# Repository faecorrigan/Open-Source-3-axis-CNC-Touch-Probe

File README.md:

# Open-Source-3-axis-CNC-Touch-Probe

This is a 3 axis cnc probe, principle development is done for the Makera Carvera

Features:
wireless communication between the probe and host via raw 802.15.4 packets
OTA firmware configuration and updates
wireless charging of on board lipo battery

The current development prototype in software uses the Arduino IDE with a seedstudio XIAO nrf52840 
Final hardware will be a custom nrf52840 circuit. 

the project currently is using public libraries from:
https://github.com/Tjoms99/xiao_sense_nrf52840_battery_lib

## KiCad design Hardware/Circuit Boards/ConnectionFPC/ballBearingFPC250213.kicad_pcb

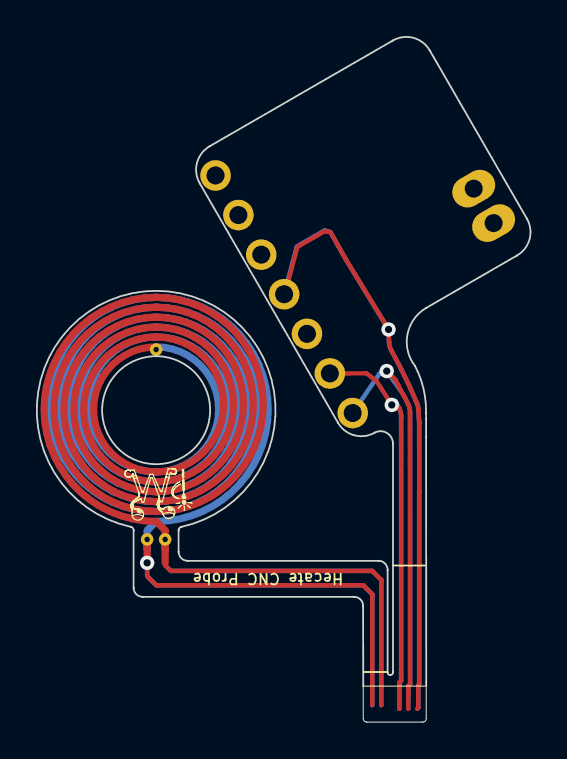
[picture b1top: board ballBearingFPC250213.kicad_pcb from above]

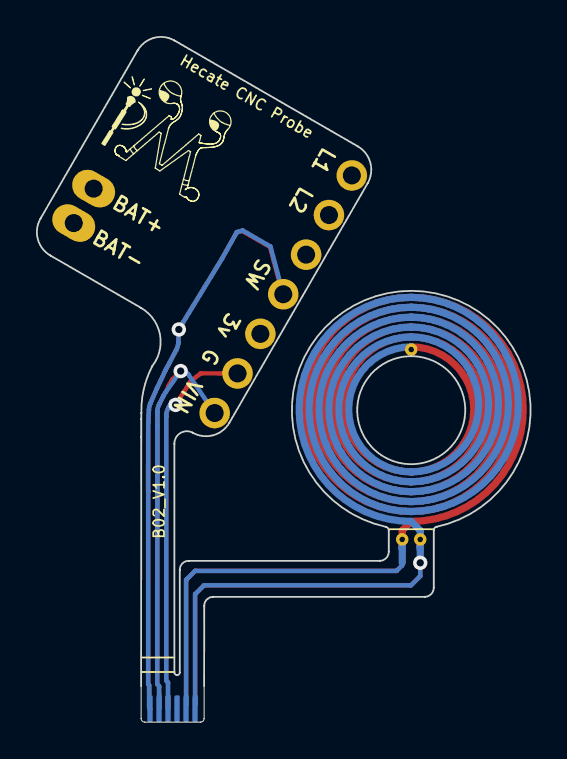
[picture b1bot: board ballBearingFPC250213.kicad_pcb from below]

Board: 2 copper layers, 27.4 x 38.1 mm, 11 parts (11 on the bottom side), 5 nets.

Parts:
J1: BB Board FPC Connection; FPC Cable End For JUSHUO AFH34 JLCPCP C5139821
J1#2: 3v; 2.54mm Flex PCB Solder Hole
J2: Xiao GND; 2.54mm Flex PCB Solder Hole
J3: Xiao VUSB; 2.54mm Flex PCB Solder Hole
J4: Xiao Switch; 2.54mm Flex PCB Solder Hole
J5: Las01; 2.54mm Flex PCB Solder Hole
J6: Las02; 2.54mm Flex PCB Solder Hole
J7: Empty; 2.54mm Flex PCB Solder Hole
J8: Bat+; 2.54mm Flex PCB Solder Hole
J9: Bat-; 2.54mm Flex PCB Solder Hole
L2: Wireless Charging Coil; COIL_GENERATOR_1

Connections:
unnamed: J1.1, J1#2.1, J4.1
unnamed: J1.2, J3.1
unnamed: J1.3, J2.1
unnamed: J1.5, L2.2
unnamed: J1.6, L2.1

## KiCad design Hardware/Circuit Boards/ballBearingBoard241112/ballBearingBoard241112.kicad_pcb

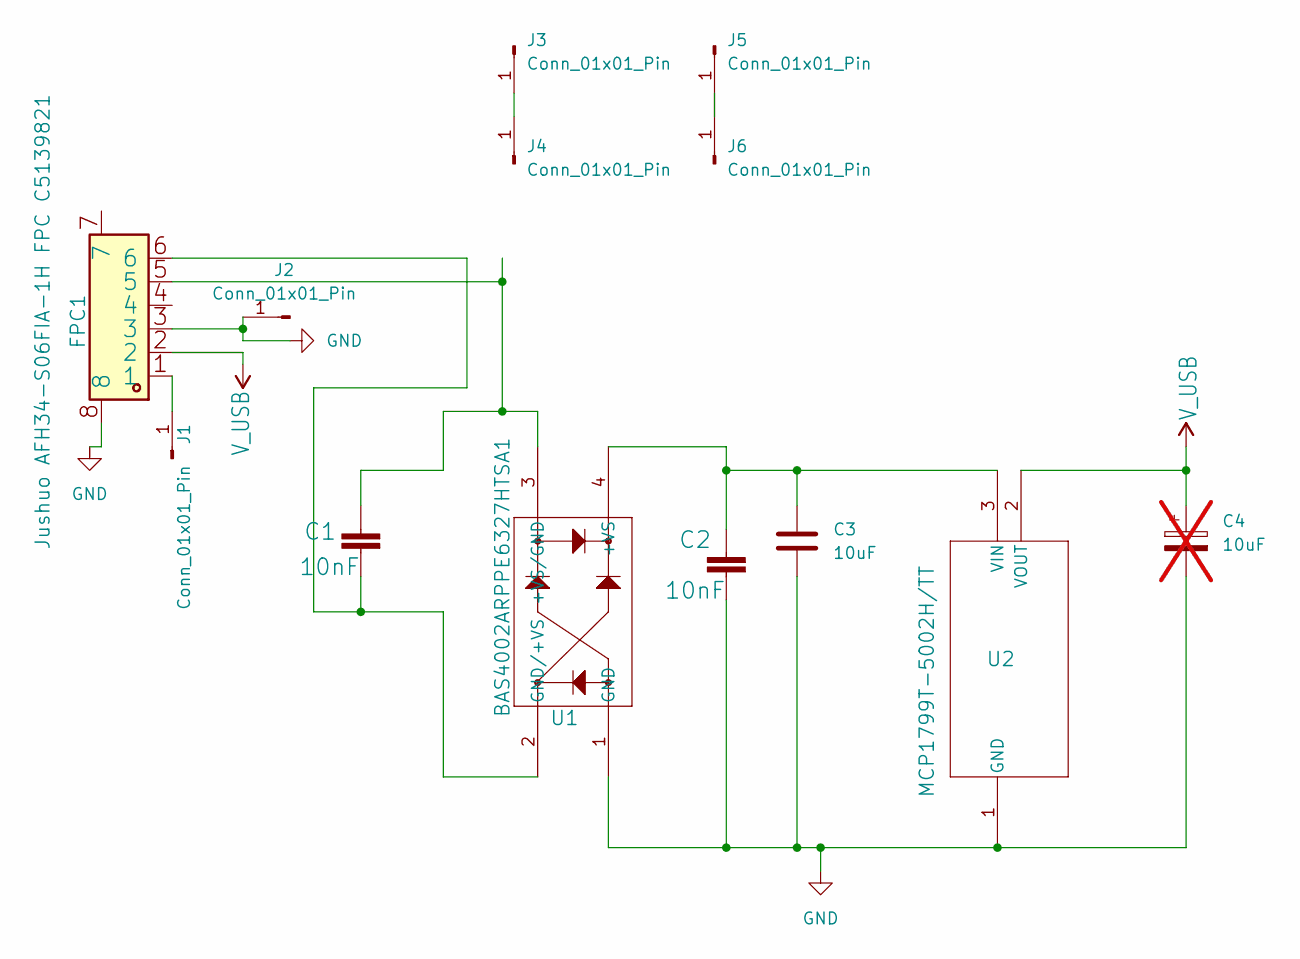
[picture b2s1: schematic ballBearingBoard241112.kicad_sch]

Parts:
C1, C2: 10nF; C_0402_1005Metric; LCSC C15195
C3: 10uF; C_0402_1005Metric; LCSC C15195
C4: 10uF; C_0603_1608Metric; not fitted
FPC1: Jushuo AFH34-S06FIA-1H FPC C5139821; LCSC C5139821
J1, J2, J3, J4, J5, J6: Conn_01x01_Pin; 0.0625 ball bearing mouting pad
U1: BAS4002ARPPE6327HTSA1; SOT143_BAS4002ARPPE6327HTSA1_INF; LCSC C3589694
U2: MCP1799T-5002H/TT; SOT-23_TT_MCH; LCSC C2890492

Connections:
GND: C2.2, C3.2, C4.2, FPC1.3, FPC1.8, J2.1, U1.1 (GND), U2.1 (GND)
unnamed: FPC1.1, J1.1
unnamed: J3.1, J4.1
unnamed: J5.1, J6.1
unnamed: C2.1, C3.1, U1.4 (+VS), U2.3 (VIN)
unnamed: C1.1, FPC1.5, U1.3 (+VS/GND)
unnamed: C1.2, FPC1.6, U1.2 (GND/+VS)
V_USB: C4.1, FPC1.2, U2.2 (VOUT)

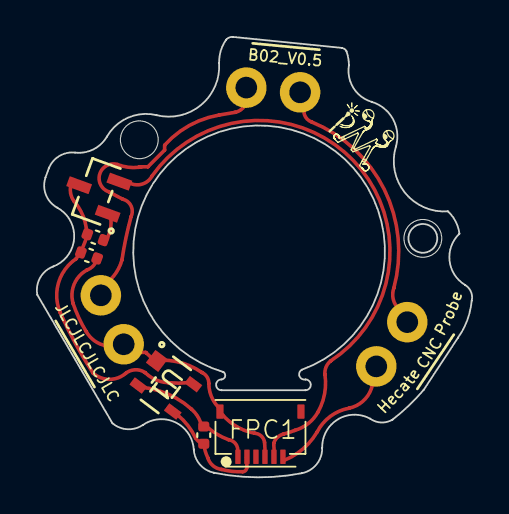
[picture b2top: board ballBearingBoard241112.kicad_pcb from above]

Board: 2 copper layers, 24.2 x 24.5 mm, 12 parts (0 on the bottom side), 8 nets.

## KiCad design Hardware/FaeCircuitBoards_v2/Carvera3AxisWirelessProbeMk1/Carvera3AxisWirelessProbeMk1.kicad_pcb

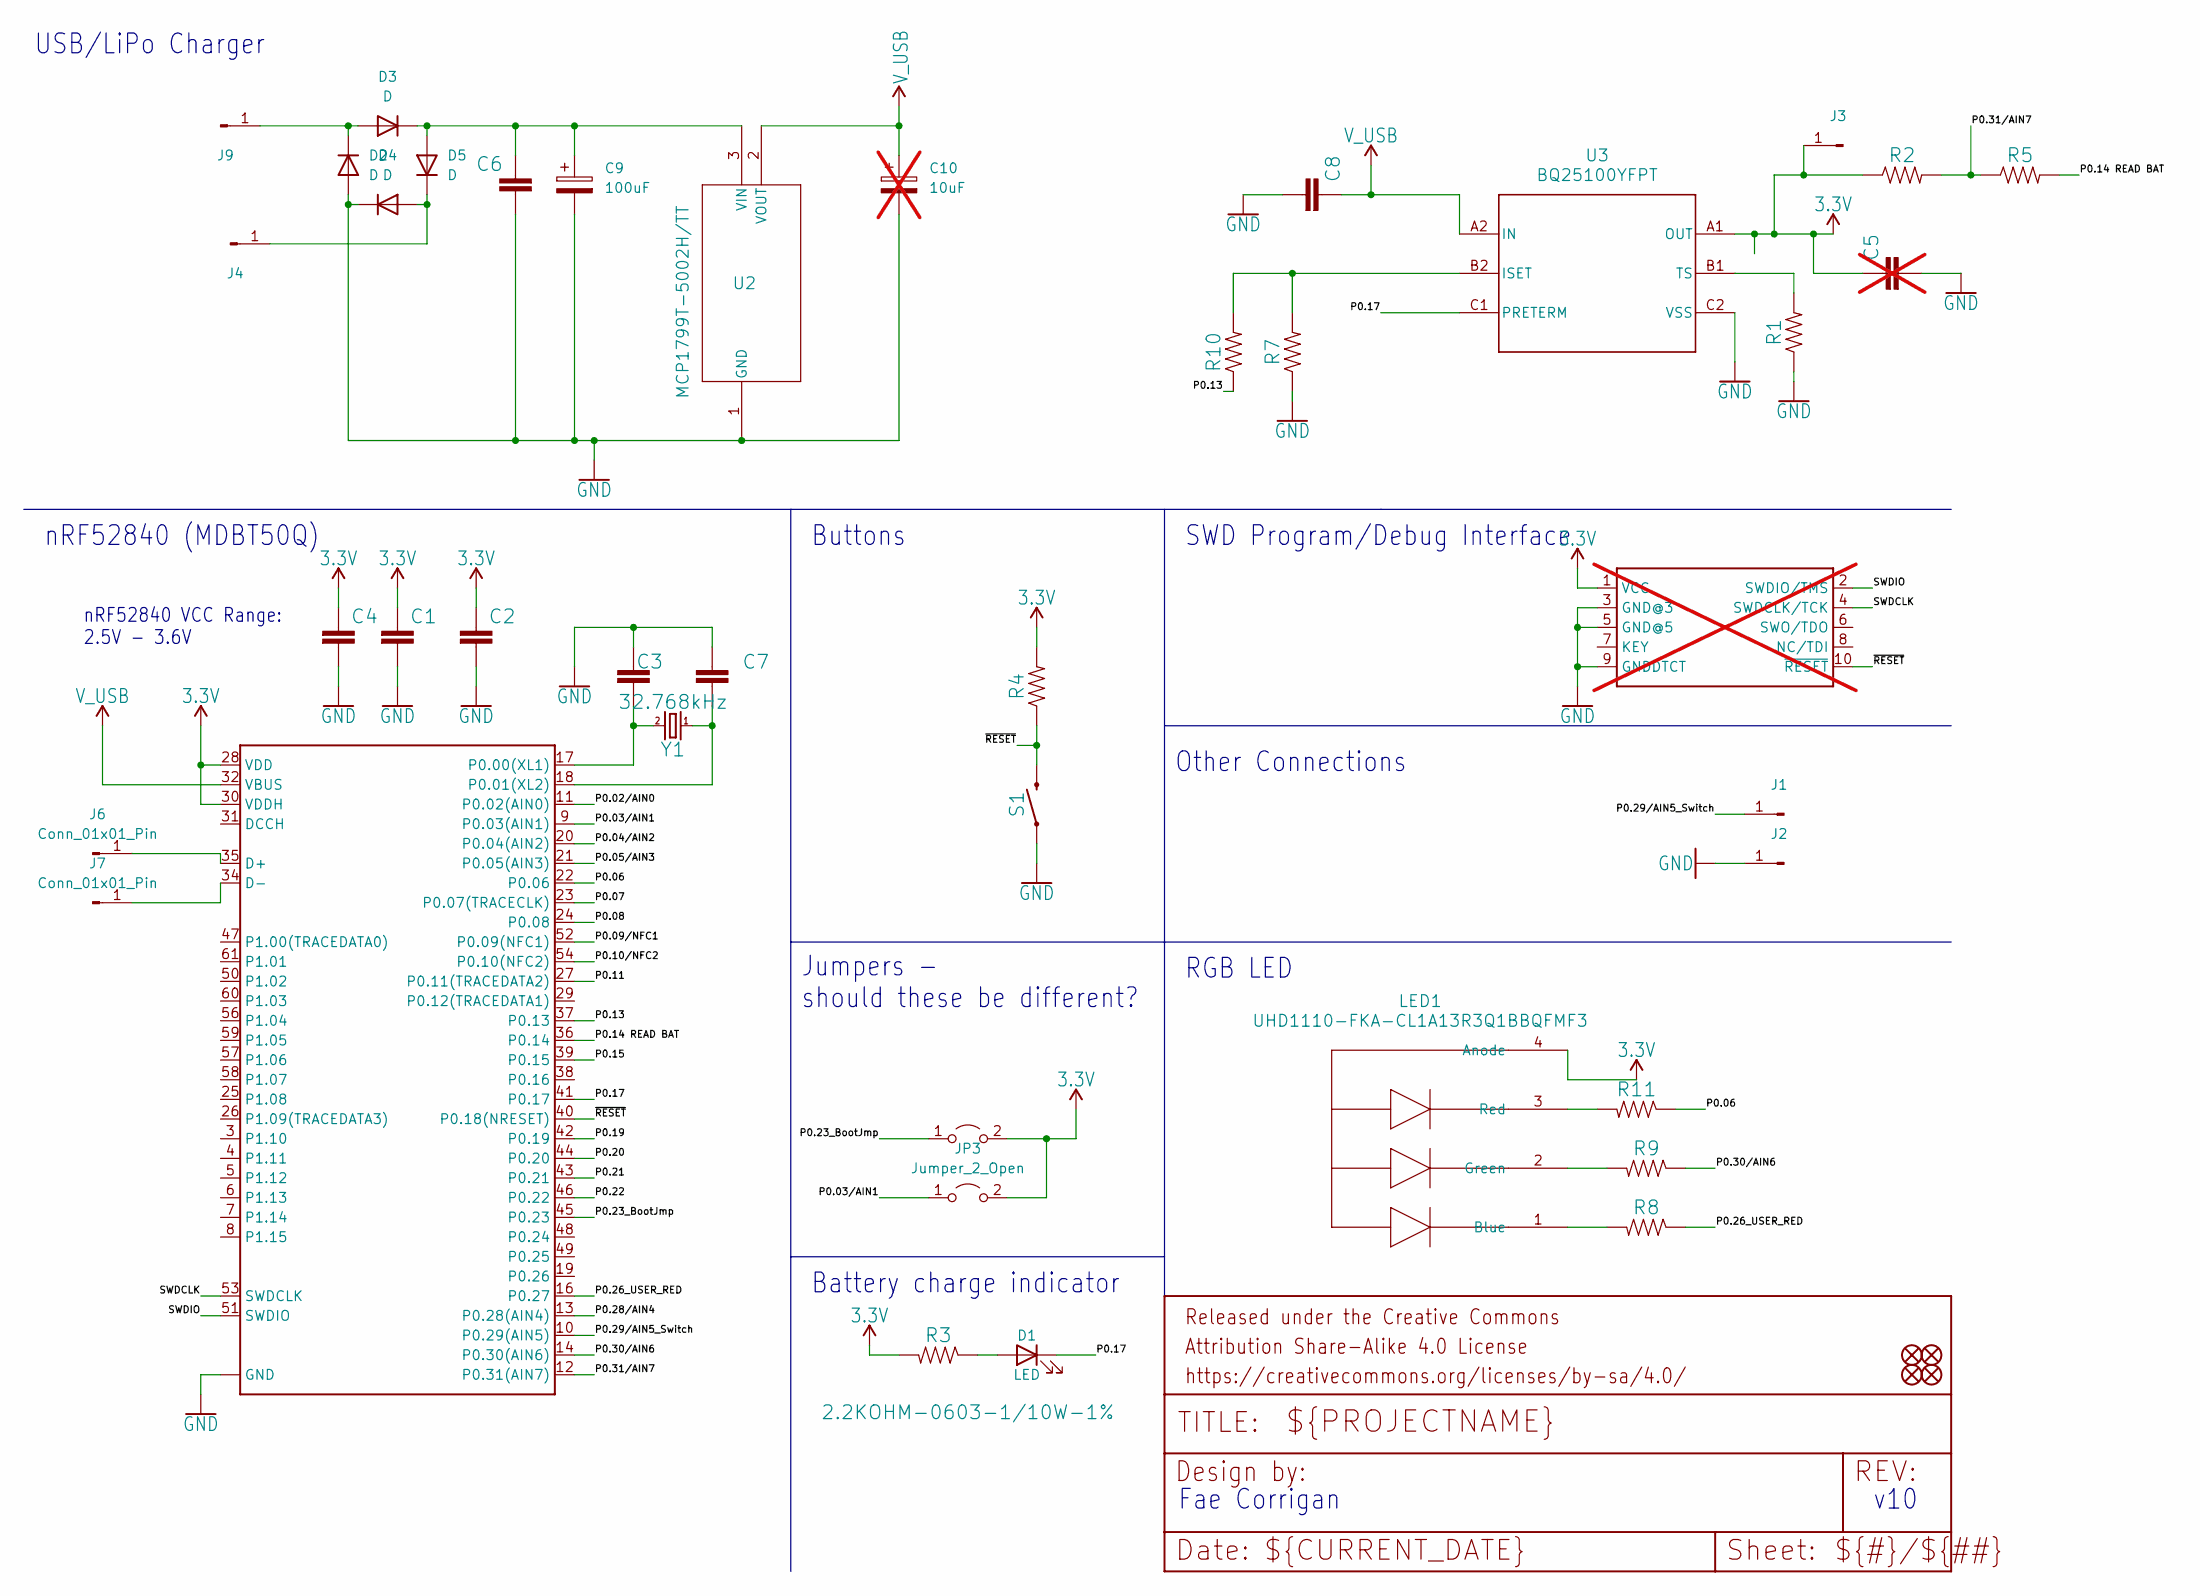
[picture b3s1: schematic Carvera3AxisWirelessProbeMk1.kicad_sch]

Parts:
C1, C4: 10UF-0603-6.3V-20%; C_0201_0603Metric
C2: 0.1UF-0603-25V-(+80/-20%); C_0201_0603Metric
C3, C7: 15PF-0603-50V-5%; C_01005_0402Metric
C5: 2.2uF; C_0201_0603Metric; not fitted
C6: 10nF; C_0402_1005Metric
C8: 2.2uF; C_0201_0603Metric
C9: 100uF; C_0402_1005Metric
C10: 10uF; C_0603_1608Metric; not fitted
D1: LED; LED_0201_0603Metric
D2, D3, D4, D5: D; D_0201_0603Metric
FD1, FD2, FD3, FD4: FIDUCIALUFIDUCIAL; FIDUCIAL-MICRO
FRAME1: FRAME-LETTER; CREATIVE_COMMONS
J1: B1; smdThroughHoleSmall
J2, J3, J4, J9: Conn_01x01_Pin; smdThroughHoleSmall
J6, J7: Conn_01x01_Pin; smdTouchPointMasked
J8: CORTEX_DEBUG_PTH; 2X5-PTH-1.27MM; not fitted
JP2: Jumper_2_Open; R_0402_1005Metric
JP3: Jumper_2_Open; R_0201_0603Metric
LED1: UHD1110-FKA-CL1A13R3Q1BBQFMF3; SON_BBQFMF3_WFS
R1: 10kOhm; R_0201_0603Metric
R2: 1MOhm; R_0201_0603Metric
R3, R8, R11: 2.2KOHM-0603-1/10W-1%; R_01005_0402Metric
R4: 10KOHM-0603-1/10W-1%; R_01005_0402Metric
R5: 510k; R_0201_0603Metric
R7, R10: 2.7Kohm; R_0201_0603Metric
R9: 10 KOhm; R_01005_0402Metric
S1: MOMENTARY-SWITCH-SPST-SMD-RIGHT-ANGLE; SW_SPST_B3U-1000P
U1: MDBT50Q
U2: MCP1799T-5002H/TT; SOT-23_TT_MCH
U3: BQ25100YFPT; YFP0006AFAV
Y1: 32.768kHz; CRYSTAL-SMD-3.2X1.5MM

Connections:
3.3V: C1.1, C2.1, C4.1, C5.1, J3.1, J8.1 (VCC), JP2.2 (B), JP3.2 (B), LED1.4 (Anode), R2.1, R3.2, R4.2, U1.28 (VDD), U1.30 (VDDH), U3.A1 (OUT)
/P0.02/AIN0: U1.11 (P0.02(AIN0))
/P0.03/AIN1: JP3.1 (A), U1.9 (P0.03(AIN1))
/P0.04/AIN2: U1.20 (P0.04(AIN2))
/P0.05/AIN3: U1.21 (P0.05(AIN3))
/P0.06: R11.1, U1.22 (P0.06)
/P0.07: U1.23 (P0.07(TRACECLK))
/P0.08: U1.24 (P0.08)
/P0.09/NFC1: U1.52 (P0.09(NFC1))
/P0.10/NFC2: U1.54 (P0.10(NFC2))
/P0.11: U1.27 (P0.11(TRACEDATA2))
/P0.13: R10.1, U1.37 (P0.13)
/P0.14 READ BAT: R5.2, U1.36 (P0.14)
/P0.15: U1.39 (P0.15)
/P0.17: D1.1 (K), U1.41 (P0.17), U3.C1 (PRETERM)
/P0.19: U1.42 (P0.19)
/P0.20: U1.44 (P0.20)
/P0.21: U1.43 (P0.21)
/P0.22: U1.46 (P0.22)
/P0.23_BootJmp: JP2.1 (A), U1.45 (P0.23)
/P0.26_USER_RED: R8.1, U1.16 (P0.27)
/P0.28/AIN4: U1.13 (P0.28(AIN4))
/P0.29/AIN5_Switch: J1.1, U1.10 (P0.29(AIN5))
/P0.30/AIN6: R9.1, U1.14 (P0.30(AIN6))
/P0.31/AIN7: R2.2, R5.1, U1.12 (P0.31(AIN7))
/SWDCLK: J8.4 (SWDCLK/TCK), U1.53 (SWDCLK)
/SWDIO: J8.2 (SWDIO/TMS), U1.51 (SWDIO)
/~RESET: J8.10 (~RESET), R4.1, S1.2, U1.40 (P0.18(NRESET))
GND: C1.2, C2.2, C3.1, C4.2, C5.2, C6.2, C7.1, C8.2, C9.2, C10.2, D2.2 (A), D4.1 (K), J2.1, J8.3 (GND@3), J8.5 (GND@5), J8.9 (GNDDTCT), R1.1, R7.1, S1.1, U1.1 (GND), U1.2 (GND), U1.15 (GND), U1.33 (GND), U1.55 (GND), U2.1 (GND), U3.C2 (VSS)
unnamed: D1.2 (A), R3.1
unnamed: D2.1 (K), D3.2 (A), J9.1
unnamed: C6.1, C9.1, D3.1 (K), D5.2 (A), U2.3 (VIN)
unnamed: D4.2 (A), D5.1 (K), J4.1
unnamed: J6.1, U1.35 (D+)
unnamed: J7.1, U1.34 (D-)
unnamed: LED1.1 (Blue), R8.2
unnamed: LED1.2 (Green), R9.2
unnamed: LED1.3 (Red), R11.2
unnamed: C3.2, U1.17 (P0.00(XL1)), Y1.P$2 (2)
unnamed: C7.2, U1.18 (P0.01(XL2)), Y1.P$1 (1)
unnamed: R7.2, R10.2, U3.B2 (ISET)
unnamed: R1.2, U3.B1 (TS)
V_USB: C8.1, C10.1, U1.32 (VBUS), U2.2 (VOUT), U3.A2 (IN)

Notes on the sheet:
Fae Corrigan
nRF52840 VCC Range: 2.5V - 3.6V
SWD Program/Debug Interface
RGB LED
USB/LiPo Charger
Battery charge indicator
v10
nRF52840 (MDBT50Q)
Buttons
Jumpers - should these be different?
Other Connections

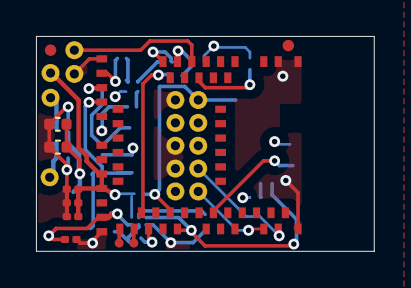
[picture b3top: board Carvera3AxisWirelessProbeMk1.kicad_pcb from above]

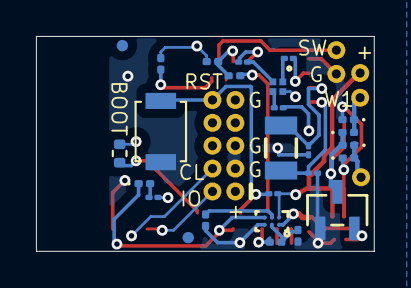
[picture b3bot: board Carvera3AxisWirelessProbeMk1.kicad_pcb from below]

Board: 4 copper layers, 18.8 x 11.9 mm, 44 parts (27 on the bottom side), 29 nets.

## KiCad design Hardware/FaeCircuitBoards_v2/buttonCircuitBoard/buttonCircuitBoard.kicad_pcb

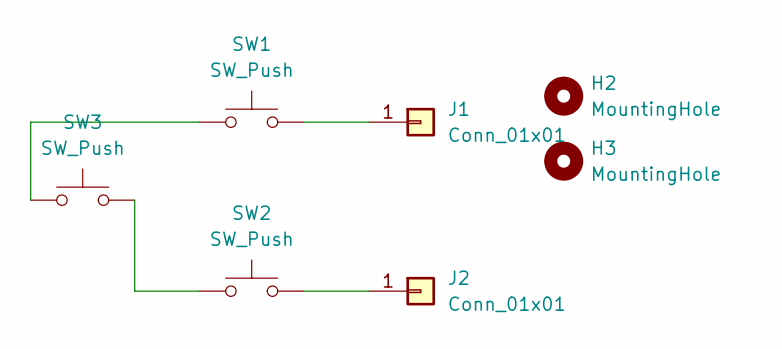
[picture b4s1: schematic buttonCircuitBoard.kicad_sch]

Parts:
H2, H3: MountingHole; 1.5mmMountingHoleNoCon
J1, J2: Conn_01x01; SolderWirePad_1x01_SMD_1x2mm
SW1, SW2, SW3: SW_Push; Ball Bearing Switch .0625 inch

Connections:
unnamed: J1.1, SW1.2
unnamed: J2.1, SW2.2
unnamed: SW1.1, SW3.1
unnamed: SW2.1, SW3.2

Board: 2 copper layers, 8 parts (0 on the bottom side), 4 nets, no tracks yet.

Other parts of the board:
H3#2: MountingHole; 1.5mmMountingHoleNoCon

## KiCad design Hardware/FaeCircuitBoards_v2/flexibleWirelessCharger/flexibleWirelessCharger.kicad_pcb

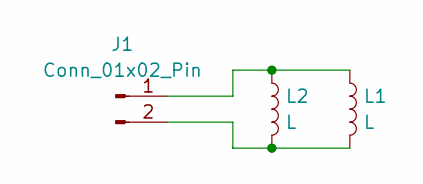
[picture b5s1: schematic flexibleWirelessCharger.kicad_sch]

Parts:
J1: Conn_01x02_Pin; TestPoint_2Pads_Pitch2.54mm_Drill0.8mm
L1: L; COIL_GENERATOR_1
L2: L; L_0603_1608Metric

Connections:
unnamed: J1.1, L1.1, L2.1
unnamed: J1.2, L1.2, L2.2

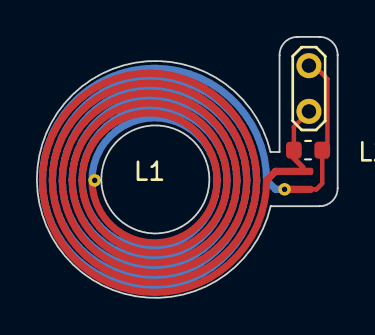
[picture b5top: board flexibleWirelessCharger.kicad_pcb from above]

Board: 2 copper layers, 16.7 x 14.5 mm, 3 parts (0 on the bottom side), 2 nets.

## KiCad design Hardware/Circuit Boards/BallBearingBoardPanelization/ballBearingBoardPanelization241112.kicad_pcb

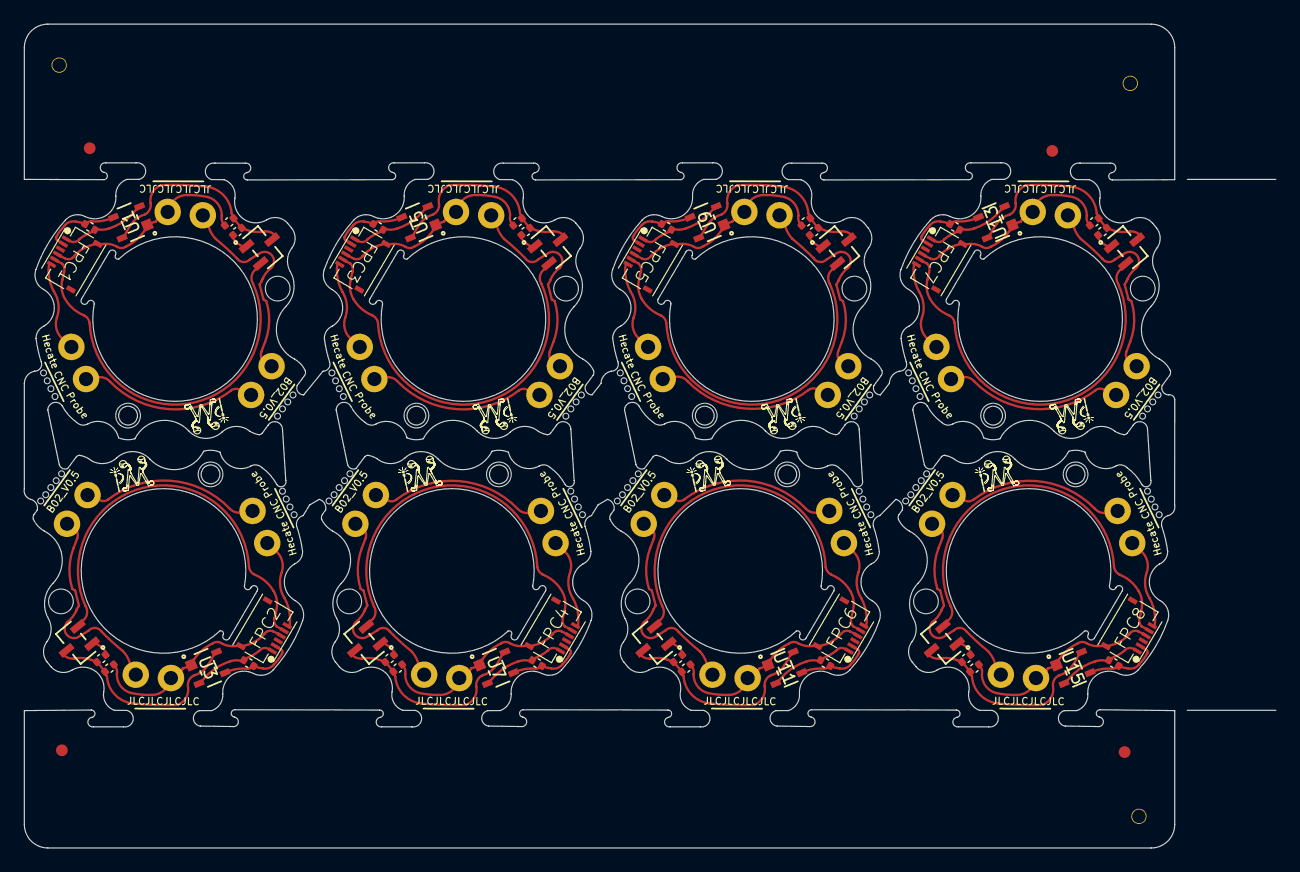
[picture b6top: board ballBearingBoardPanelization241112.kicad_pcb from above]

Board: 2 copper layers, 106.4 x 70.0 mm, 147 parts (0 on the bottom side), 8 nets.

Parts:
1, 2, 3, 4, 5, 6, 7, 8, 9, 10, 11, 12, 13, 14, 15, 16, 17, 18, 19, 20, 21, 22, 23, 24, 25, 26, 27, 28, 29, 30, 31, 32, 33, 34, 35, 36, 37, 38, 39, 40, 41, 42, 43, 44, 45, 46, 47, 48, 49, 50, 51: (no value)
C1, C2, C5, C6, C7, C8, C11, C12, C13, C14, C17, C18, C19, C20, C23, C24: 10nF; C_0402_1005Metric
C3, C4, C9, C10, C15, C16, C21, C22: 10uF; C_0402_1005Metric
FPC1, FPC2, FPC3, FPC4, FPC5, FPC6, FPC7, FPC8: XUNPU_FPC-05F-6PH20_JLCPCB_C2856796; Jushuo AFH34-S06FIA-1H FPC C5139821
J1, J1#2, J2, J2#2, J3, J3#2, J4, J4#2, J5, J5#2, J6, J6#2, J7, J8, J9, J10, J11, J12, J13, J14, J15, J16, J17, J18, J19, J20, J21, J22, J23, J24, J25, J26, J27, J28, J29, J30, J31, J32, J33, J34, J35, J36, J37, J38, J39, J40, J41, J42: Conn_01x01_Pin; 0.0625 ball bearing mouting pad
U1, U3, U5, U7, U9, U11, U13, U15: BAS4002ARPPE6327HTSA1; SOT143_BAS4002ARPPE6327HTSA1_INF
U2, U4, U6, U8, U10, U12, U14, U16: MCP1799T-5002H/TT; SOT-23_TT_MCH

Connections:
GND: C2.2, C3.2, C4.2, C5.2, C8.2, C9.2, C10.2, C11.2, C14.2, C15.2, C16.2, C17.2, C20.2, C21.2, C22.2, C23.2, FPC1.3, FPC1.8, FPC2.3, FPC2.8, FPC3.3, FPC3.8, FPC4.3, FPC4.8, FPC5.3, FPC5.8, FPC6.3, FPC6.8, FPC7.3, FPC7.8, FPC8.3, FPC8.8, J2.1, J2#2.1, J9.1, J10.1, J21.1, J22.1, J33.1, J34.1, U1.1 (GND), U2.1 (GND), U3.1 (GND), U4.1 (GND), U5.1 (GND), U6.1 (GND), U7.1 (GND), U8.1 (GND), U9.1 (GND), U10.1 (GND), U11.1 (GND), U12.1 (GND), U13.1 (GND), U14.1 (GND), U15.1 (GND), U16.1 (GND)
unnamed: FPC1.1, FPC2.1, FPC3.1, FPC4.1, FPC5.1, FPC6.1, FPC7.1, FPC8.1, J1.1, J1#2.1, J7.1, J8.1, J19.1, J20.1, J31.1, J32.1
unnamed: J3.1, J3#2.1, J4.1, J4#2.1, J11.1, J12.1, J13.1, J14.1, J23.1, J24.1, J25.1, J26.1, J35.1, J36.1, J37.1, J38.1
unnamed: J5.1, J5#2.1, J6.1, J6#2.1, J15.1, J16.1, J17.1, J18.1, J27.1, J28.1, J29.1, J30.1, J39.1, J40.1, J41.1, J42.1
unnamed: C2.1, C3.1, C4.1, C5.1, C8.1, C9.1, C10.1, C11.1, C14.1, C15.1, C16.1, C17.1, C20.1, C21.1, C22.1, C23.1, U1.4 (+VS), U2.3 (VIN), U3.4 (+VS), U4.3 (VIN), U5.4 (+VS), U6.3 (VIN), U7.4 (+VS), U8.3 (VIN), U9.4 (+VS), U10.3 (VIN), U11.4 (+VS), U12.3 (VIN), U13.4 (+VS), U14.3 (VIN), U15.4 (+VS), U16.3 (VIN)
unnamed: C1.1, C6.1, C7.1, C12.1, C13.1, C18.1, C19.1, C24.1, FPC1.5, FPC2.5, FPC3.5, FPC4.5, FPC5.5, FPC6.5, FPC7.5, FPC8.5, U1.3 (+VS/GND), U3.3 (+VS/GND), U5.3 (+VS/GND), U7.3 (+VS/GND), U9.3 (+VS/GND), U11.3 (+VS/GND), U13.3 (+VS/GND), U15.3 (+VS/GND)
unnamed: C1.2, C6.2, C7.2, C12.2, C13.2, C18.2, C19.2, C24.2, FPC1.6, FPC2.6, FPC3.6, FPC4.6, FPC5.6, FPC6.6, FPC7.6, FPC8.6, U1.2 (GND/+VS), U3.2 (GND/+VS), U5.2 (GND/+VS), U7.2 (GND/+VS), U9.2 (GND/+VS), U11.2 (GND/+VS), U13.2 (GND/+VS), U15.2 (GND/+VS)
V_USB: FPC1.2, FPC2.2, FPC3.2, FPC4.2, FPC5.2, FPC6.2, FPC7.2, FPC8.2, U2.2 (VOUT), U4.2 (VOUT), U6.2 (VOUT), U8.2 (VOUT), U10.2 (VOUT), U12.2 (VOUT), U14.2 (VOUT), U16.2 (VOUT)

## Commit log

2024-04-22 initial push of early prototype from Fae
    there will be further updates for hardware and circuit boards this week
2024-04-22 initial commit: dump probe captures and analysis script
2024-04-22 initial commit: bare metal arm firmware for the probe
2024-04-22 makera carvera fusion post processor for scratch drive
2024-04-23 test for kinematic mounts for ball bearings + circuit board contact
2024-04-24 wip probe state machine
2024-04-26 update analyze script to print packet information more cleanly
2024-04-26 utility for writing/erasing flash
2024-04-27 call and response pairing example
    gets very close but fails to actually finish pairing. There are some shenanigans happening on channel 26 that could be the culprit
2024-04-27 current probe firmware test
2024-04-29 scratch firmware update
2024-05-17 updating core firmware for probe
2024-05-17 quick refactor of code
2024-06-06 programming board
2024-10-31 Create LICENSE
    software is MIT, Hardware is CC BY-SA-NC
2024-11-10 implement 3uA system on sleep during idle
2024-11-11 Sleep mode update
    fixing some hiccups with sleep mode disabling pairing mode/sending packets in general.
    Current bugs to squash:
    deep sleep mode is triggered but never entered properly. It just lives in the infinite loop printing "off"
    This appears to be a problem with idlemode as the deep sleep works when entered directly via another method
    idle mode is not polling the probe pin frequently enough. It will only wake up if the probe is triggered while it is sending a heartbeat.
    We should consider setting up the probe pin as an interrupt when it is in idle mode.
2024-11-11 improving state machine
2024-11-11 sleep mode button interrupt fix
2025-01-20 finished, works
2025-01-20 configure laser pins for output
2025-01-20 restore system-off deep sleep functionality
2025-01-20 add optional pin number overrides
2025-01-20 clean up sleep/interrupt handling code
2025-01-20 clean up packet building/sending
2025-01-20 add more optional pin number overrides
2025-01-20 safety check to ensure lasers are off while sleeping
    I think this changes nothing under default configuration, but if a user
    configures a longer laserDelay than idleDelay (invalid configuration)
    it's important. Also generally just good hygiene
2025-01-20 decrease complixity of pairing function
2025-01-28 fix millis()
2025-01-29 implement mill-initiated laser on command
2025-02-02 send heart beats during probe active mode if it's time, including first heartbeat after power on
2025-02-02 cleanup
2025-02-03 actually save paired info to flash, and read it on boot
2025-02-03 make sequence number behavior match stock probe
2025-02-04 rewrite handling of seq to match carvera behavior. Increase probe packet rate to match too
2025-02-08 modify heartbeat rate to match carvera, and sleep time to be reasonably long
2025-02-08 match probe 0x06 behavior: read battery and send 0x06 after every wake from idle
2025-02-11 check at the beginning of pairing cycle if the button is pressed
2025-02-11 low power peripherals: external-only button pullup and only enable vbat_read when using it
2025-02-13 implement low power mode, validate pair, trigger, heart beat, laser functions
2025-11-08 Updating Probe Circuit Boards to Latest
2025-11-13 Fusion File

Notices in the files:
Hardware/FaeCircuitBoards_v2/Carvera3AxisWirelessProbeMk1/Carvera3AxisWirelessProbeMk1.kicad_sch:
https://creativecommons.org/licenses/by-sa/4.0
Released under the Creative Commons
parts and their libraries:
Released under the Creative Commons Attribution Share-Alike 4.0 License
